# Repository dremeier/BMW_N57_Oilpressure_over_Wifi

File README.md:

# BMW N57 Oilpressure over WiFi

Öldruck- und Öltemperaturanzeige für BMW N57 Motoren auf Basis eines ESP32  
mit eigenem PCB, VDO-Öldrucksensor und Web-UI (Dark-OLED / Kombiinstrument-Stil).

---
## 📸 Projektüberblick

### Komplettsystem – Steuergerät & Sensor

Das System besteht aus einem ESP32-Steuergerät und einer separaten
Sensorplatine, die direkt am VDO-Öldruckgeber montiert ist.  
Die Anzeige erfolgt drahtlos über ein integriertes Web-Interface.

---
### Steuergerät (ESP32-S3 Mini)

## Features

- Messung des **Öldrucks (0–5 bar)** über VDO Druckgeber  
- Messung der **Öltemperatur** (DS18B20)  
- **ESP32 Web-Interface** (kein Internet erforderlich)  
- Automatisches **Tag-/Nacht-Design** (Grün / BMW-Amber)  
- Analoge Rundinstrument-Anzeige (Skala 0–5 bar)  
- Warnlogik:  
  - Öldruck < 0,8 bar → blinkende Warnanzeige  
  - Öltemperatur > Schwellwert → Warnfarbe  
- Integriertes **Debug-Overlay** (ADC, Spannung, Widerstände, Versionen)

---

### VDO Öldruckgeber montiert

OEM-naher VDO-Öldruckgeber mit integrierter Elektronik und KFZ-tauglicher
Montage.

---

## Projektstruktur

```text
BMW_N57_OILPRESSURE_OVER_WIFI/
├─ firmware/          ESP32 Firmware (PlatformIO)
├─ pcb_main/          Hauptplatine (KiCad)
├─ pcb_sensor/        Sensorplatine (KiCad)
├─ docs/              Datenblätter & Dokumentation
└─ README.md
```

---
### 3D-Render – Hauptplatine

3D-Ansicht der Hauptplatine (KiCad).  
Kompaktes, robustes Layout für den Einsatz im Fahrzeug.

## Hardware

- ESP32 (ESP32-S3 mini)
- VDO Öldruckgeber 0–5 bar (M12x1.5)
- DS18B20 Temperatursensor
- Step‑Down‑Regler 
- Versorgung Sensor: **≈ 5,0 V**
- USB‑C zum flaschen

## 🚦 Status-LEDs

| LED | Funktion |
|----|---------|
| **LED orange** | Leuchtet dauerhaft, wenn der WiFi-Access-Point aktiv ist |
| **LED blau** | Leuchtet, sobald ein Client (Smartphone / Browser) verbunden ist |

---

## Messprinzip

Der VDO-Öldruckgeber arbeitet als Widerstand gegen Masse.  
Die Messung erfolgt über einen Spannungsteiler:

```text
+5V → R_PULLUP → Rsensor → GND
```

Die Firmware berechnet:
1. ADC → Spannung (kalibriert)
2. Spannung → Rsensor
3. Rsensor → bar (VDO-Kennlinie via LUT + Interpolation)
4. IIR-Filter zur Glättung

---
### Web-UI (Live-Anzeige)

## Web-UI

- Zugriff über ESP32 Access Point
- Anzeige:
  - Öldruck (bar)
  - Öltemperatur (°C)
  - Analoges Rundinstrument
- Debug-Bereich mit:
  - ADC
  - Vadc
  - Rsensor
  - Bar raw
  - ESP-Temperatur
  - Versorgungsspannung
  - Pullup-Widerstand
  - SW- / HW-Version

---

## Status

- Hardware: **funktionsfähig**
- Firmware: **stabil**
- Kalibrierung: **ADC + Versorgungsspannung kalibriert**
- Projektstatus: **aktiv in Entwicklung**

---

## Hinweis

Dieses Projekt ist ein **DIY-Projekt** und ersetzt keine serienmäßigen
Sicherheitsfunktionen des Fahrzeugs.

Nutzung auf eigene Verantwortung.

---

## Lizenz

Noch nicht festgelegt.

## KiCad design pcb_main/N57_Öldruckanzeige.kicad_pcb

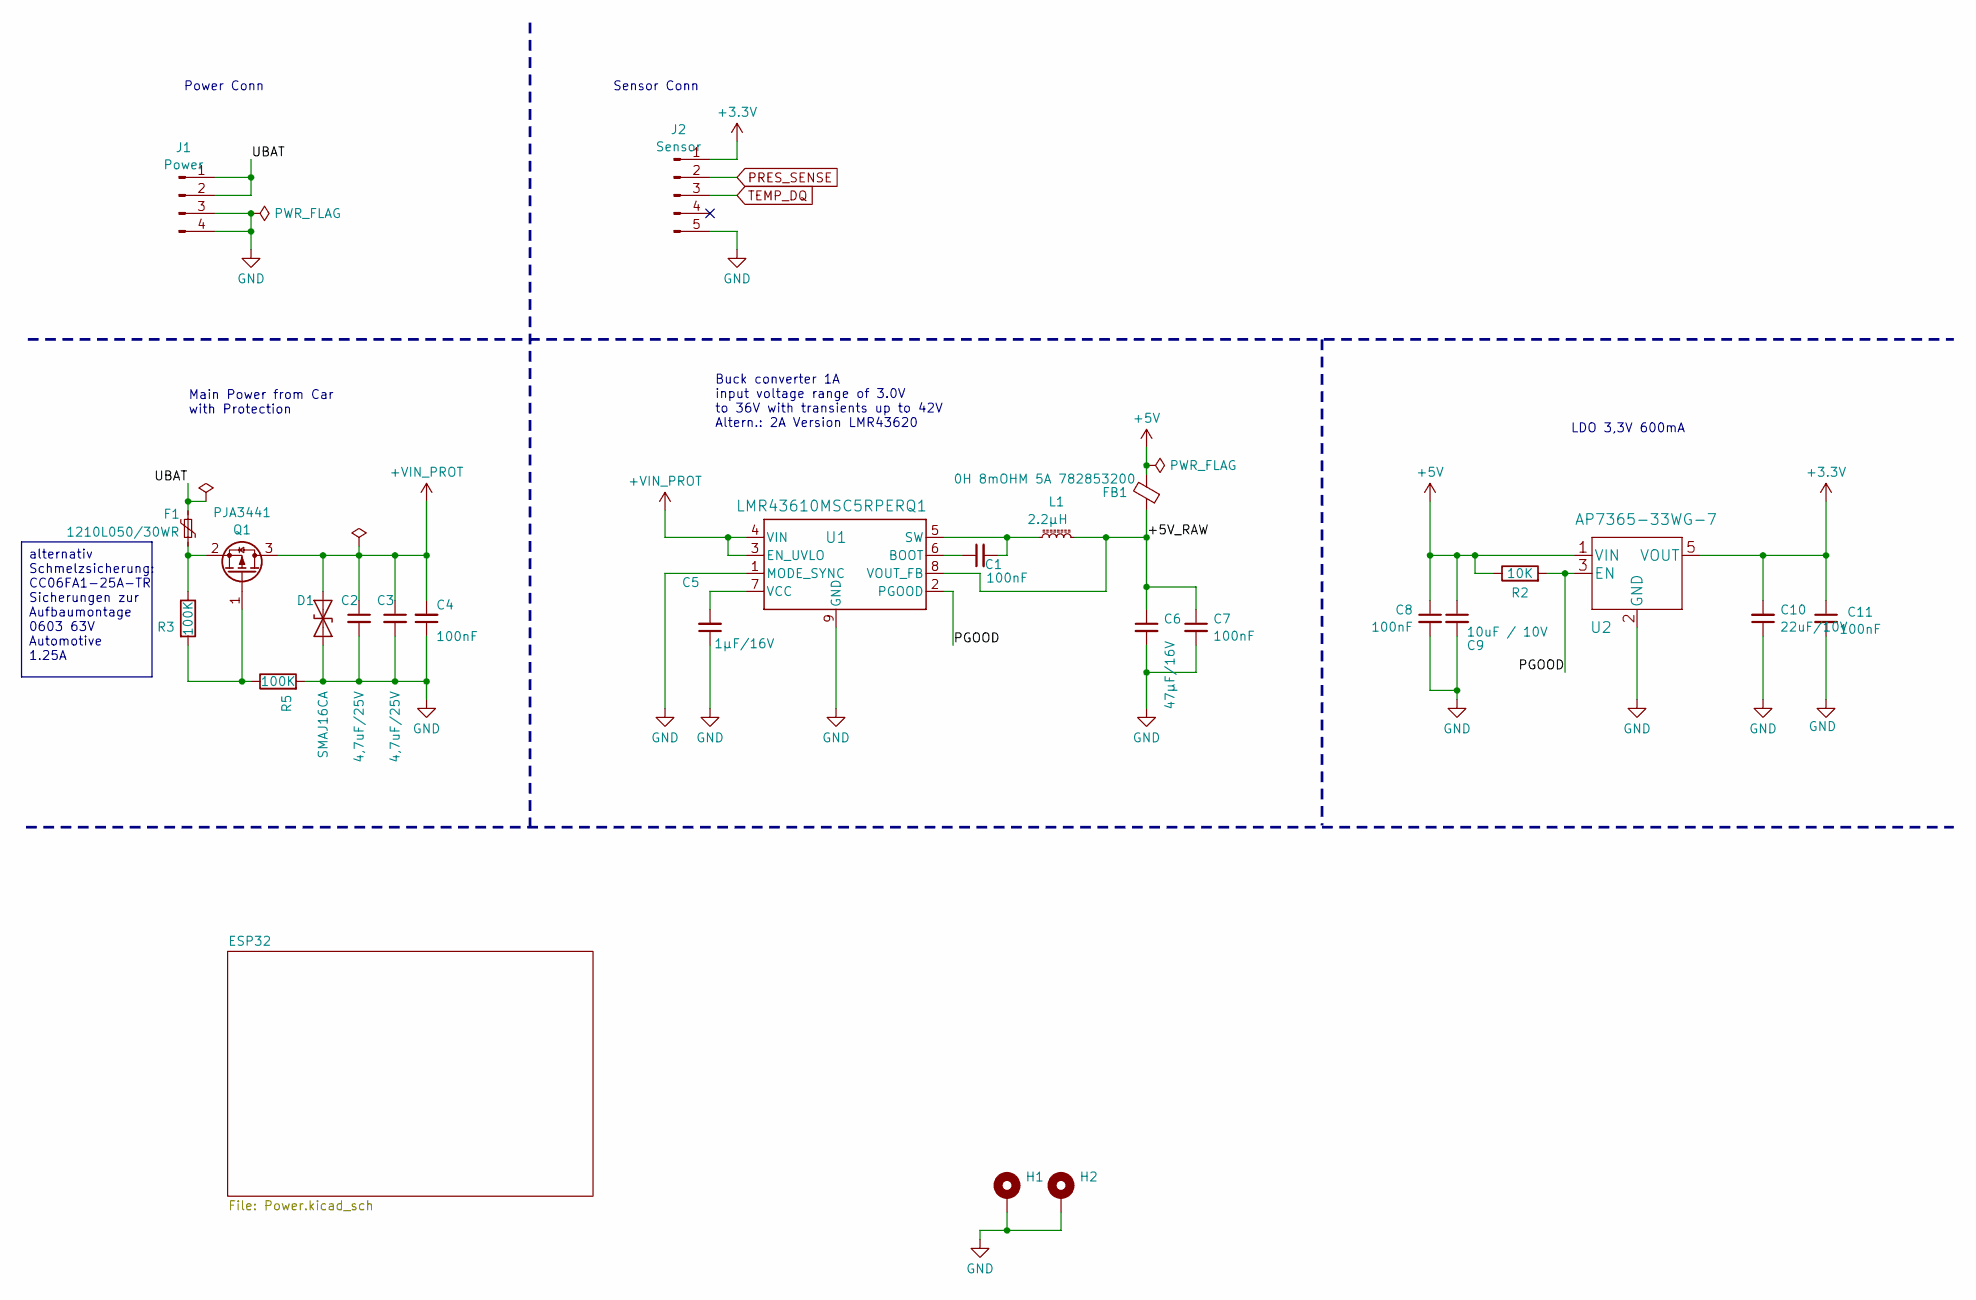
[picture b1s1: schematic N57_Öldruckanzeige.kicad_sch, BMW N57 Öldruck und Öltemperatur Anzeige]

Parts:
C1, C4, C7, C8, C11: 100nF; C_0603_1608Metric; my_parts_ID 5; LCSC C14663
C2, C3: 4,7uF/25V; C_0805_2012Metric; my_parts_ID 37; LCSC C98195
C5: 1μF/16V; C_0603_1608Metric; my_parts_ID 22; LCSC C5199872
C6: 47µF/16V; C_1210_3225Metric; Part Number MBASE32MAB5476KPNDT1; LCSC C77101
C9: 10uF / 10V; C_0805_2012Metric; Part Number GRM21BR71A106KA73K; LCSC C32635
C10: 22uF/10V; C_0603_1608Metric; Part Number GRT188R61A226ME13D; LCSC C86295
D1: SMAJ16CA; D_SMA; Part Number SMAJ40CA-TR; LCSC C148226
F1: 1210L050/30WR; Fuse_1210_3225Metric; Part Number 1210L050/30WR; LCSC C2154034
FB1: 0H 8mOHM 5A 782853200; L_Eaton_MCL2012V1; my_parts_ID 80; LCSC C394484
H1, H2: MountingHole_Pad; MountingHole_3.2mm_M3_ISO7380_Pad
J1: Power; JST_PH_S4B-PH-K_1x04_P2.00mm_Horizontal
J2: Sensor; JST_PH_S5B-PH-K_1x05_P2.00mm_Horizontal
L1: 2.2µH; L_Coilcraft_XxL4040; Part Number XEL4020-222MEC; LCSC C3151182
Q1: PJA3441; SOT-23-3; my_parts_ID 296; LCSC C313504
R2: 10K; R_0603_1608Metric; my_parts_ID 236; LCSC C98220
R3: 100K; R_0603_1608Metric; my_parts_ID 200; LCSC C98220
R5: 100K; R_0603_1608Metric; my_parts_ID 250; LCSC C98220
U1: LMR43610MSC5RPERQ1; LMR43610; Part Number LM61495Q5RPHRQ1; LCSC C5219291
U2: AP7365-33WG-7; SOT-23-5; Part Number AP7365-33WG-7; LCSC C150742

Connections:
+3.3V: C10.2, C11.1, J2.1, U2.5 (VOUT); also elsewhere on the board
+5V: C8.1, C9.1, FB1.2, R2.1, U2.1 (VIN); also elsewhere on the board
+VIN_PROT: C2.1, C3.1, C4.2, D1.2 (A2), Q1.3 (D), U1.3 (EN_UVLO), U1.4 (VIN)
/+5V_RAW: C6.1, C7.1, FB1.1, L1.2, U1.8 (VOUT_FB)
/PGOOD: R2.2, U1.2 (PGOOD), U2.3 (EN)
/UBAT: F1.2, J1.1, J1.2
GND: C2.2, C3.2, C4.1, C5.1, C6.2, C7.2, C8.2, C9.2, C10.1, C11.2, D1.1 (A1), H1.1, H2.1, J1.3, J1.4, J2.5, R5.2, U1.1 (MODE_SYNC), U1.9 (GND), U2.2 (GND); also elsewhere on the board
unnamed: Q1.1 (G), R3.2, R5.1
unnamed: F1.1, Q1.2 (S), R3.1
unnamed: C1.1, U1.6 (BOOT)
unnamed: C1.2, L1.1, U1.5 (SW)
unnamed: C5.2, U1.7 (VCC)
PRES_SENSE: J2.2; also elsewhere on the board
TEMP_DQ: J2.3; also elsewhere on the board

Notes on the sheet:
Sensor Conn
Main Power from Car with Protection
Power Conn
LDO 3,3V 600mA
Buck converter 1A input voltage range of 3.0V to 36V with transients up to 42V Altern.: 2A Version LMR43620
alternativ Schmelzsicherung: CC06FA1-25A-TR Sicherungen zur Aufbaumontage 0603 63V Automotive 1.25A

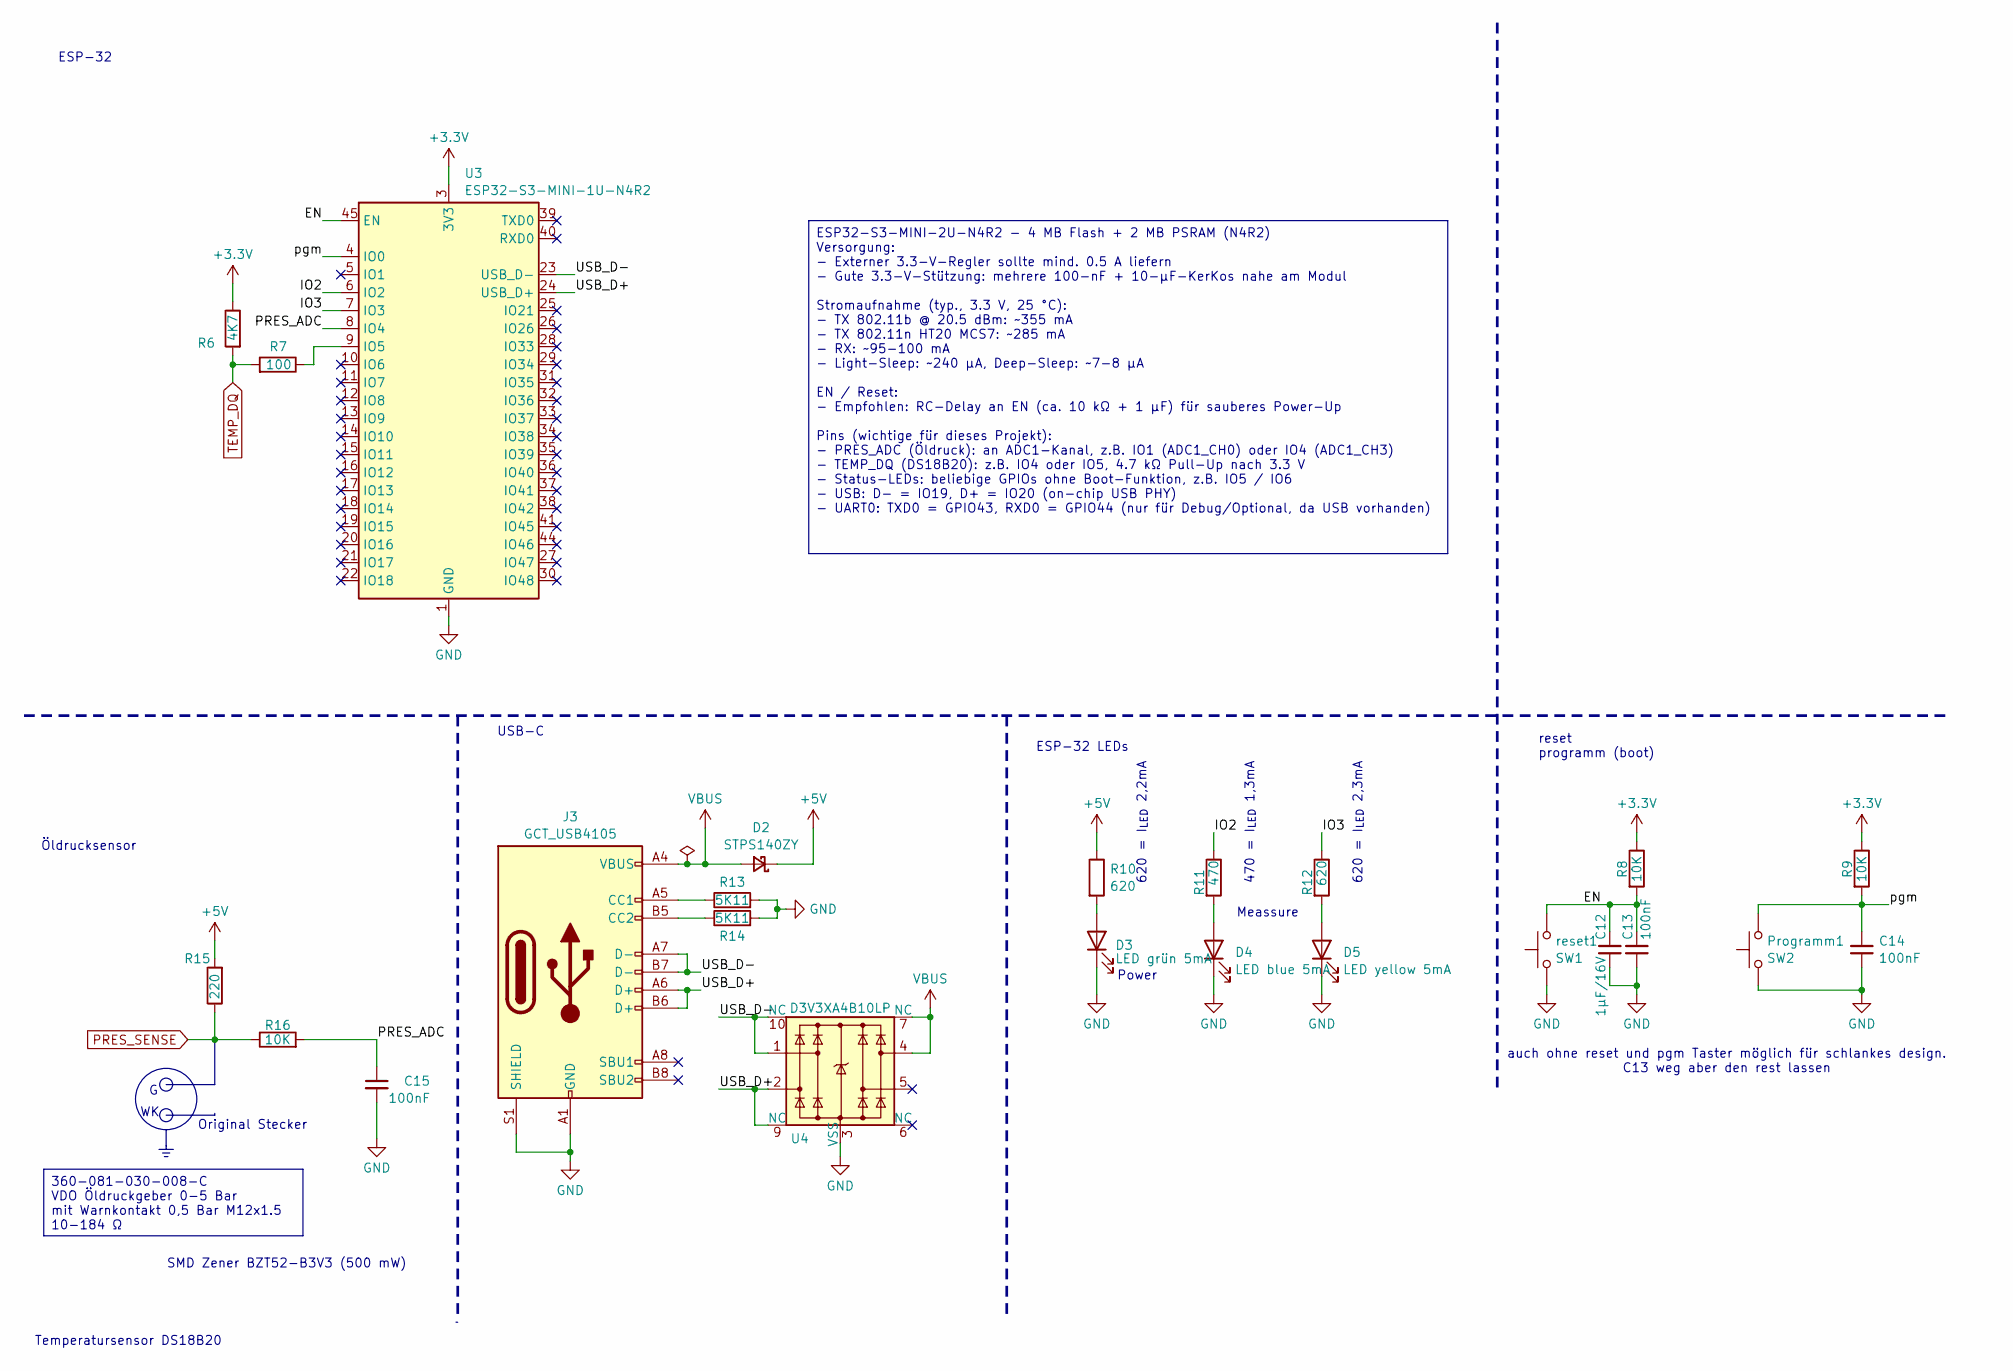
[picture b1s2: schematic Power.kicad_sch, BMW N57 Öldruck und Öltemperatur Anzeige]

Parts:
C12: 1μF/16V; C_0603_1608Metric; my_parts_ID 22; LCSC C5199872
C13, C14, C15: 100nF; C_0603_1608Metric; my_parts_ID 5; LCSC C14663
D2: STPS140ZY; D_SOD-123; my_parts_ID 71; LCSC C155662
D3: LED grün 5mA; LED_0603_1608Metric; my_parts_ID 184; LCSC C2962098
D4: LED blue 5mA; LED_0603_1608Metric; my_parts_ID 182; LCSC C125103
D5: LED yellow 5mA; LED_0603_1608Metric; my_parts_ID 183; LCSC C160477
J3: GCT_USB4105; USB_C_Receptacle_GCT_USB4105-xx-A_16P_TopMnt_Horizontal; Part Number USB4105-GF-A-120; LCSC C5184243
Programm1: SW2; SW_Push_1P1T_NO_Vertical_Wuerth_434133025816; Part Number RKB2SJK250SMTR; LCSC C2927789
R6: 4K7; R_0603_1608Metric; my_parts_ID 246; LCSC C99782
R7: 100; R_0603_1608Metric; my_parts_ID 200; LCSC C105588
R8, R9: 10K; R_0603_1608Metric; my_parts_ID 236; LCSC C98220
R10, R12: 620; R_0603_1608Metric; my_parts_ID 220; LCSC C137695
R11: 470; R_0603_1608Metric; my_parts_ID 216; LCSC C114669
R13, R14: 5K11; R_0603_1608Metric; my_parts_ID 233; LCSC C112314
R15: 220; R_0603_1608Metric; my_parts_ID 207; LCSC C107696
R16: 10K; R_0603_1608Metric; my_parts_ID 207; LCSC C107696
U3: ESP32-S3-MINI-1U-N4R2; ESP32-S2-MINI-1U; my_parts_ID 298; LCSC C22356044
U4: D3V3XA4B10LP; Diodes_UDFN-10_1.0x2.5mm_P0.5mm; Part Number D3V3XA4B10LP-7; LCSC C1980462
reset1: SW1; SW_Push_1P1T_NO_Vertical_Wuerth_434133025816; Part Number RKB2SJK250SMTR; LCSC C2927789

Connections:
+3.3V: R6.1, R8.1, R9.1, U3.3 (3V3); also elsewhere on the board
+5V: D2.1 (K), R10.1, R15.2; also elsewhere on the board
/ESP32/EN: C12.2, C13.2, R8.2, U3.45 (EN), reset1.2
/ESP32/IO2: R11.1, U3.6 (IO2)
/ESP32/IO3: R12.1, U3.7 (IO3)
/ESP32/PRES_ADC: C15.1, R16.2, U3.8 (IO4)
/ESP32/USB_D+: J3.A6 (D+), J3.B6 (D+), U3.24 (USB_D+), U4.2, U4.9 (NC)
/ESP32/USB_D-: J3.A7 (D-), J3.B7 (D-), U3.23 (USB_D-), U4.1, U4.10 (NC)
/ESP32/pgm: C14.2, Programm1.2, R9.2, U3.4 (IO0)
GND: C12.1, C13.1, C14.1, C15.2, D3.1 (K), D4.1 (K), D5.1 (K), J3.A1 (GND), J3.A12 (GND), J3.B1 (GND), J3.B12 (GND), J3.S1 (SHIELD), Programm1.1, R13.2, R14.2, U3.1 (GND), U3.2 (GND), U3.42 (GND), U3.43 (GND), U3.46 (GND), U3.47 (GND), U3.48 (GND), U3.49 (GND), U3.50 (GND), U3.51 (GND), U3.52 (GND), U3.53 (GND), U3.54 (GND), U3.55 (GND), U3.56 (GND), U3.57 (GND), U3.58 (GND), U3.59 (GND), U3.60 (GND), U3.61 (GND), U3.62 (GND), U3.63 (GND), U3.64 (GND), U3.65 (GND), U4.3 (VSS), reset1.1; also elsewhere on the board
unnamed: D3.2 (A), R10.2
unnamed: D4.2 (A), R11.2
unnamed: D5.2 (A), R12.2
unnamed: J3.A5 (CC1), R13.1
unnamed: J3.B5 (CC2), R14.1
unnamed: R7.1, U3.9 (IO5)
PRES_SENSE: R15.1, R16.1; also elsewhere on the board
TEMP_DQ: R6.2, R7.2; also elsewhere on the board
VBUS: D2.2 (A), J3.A4 (VBUS), J3.A9 (VBUS), J3.B4 (VBUS), J3.B9 (VBUS), U4.4, U4.7 (NC)

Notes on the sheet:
auch ohne reset und pgm Taster möglich für schlankes design. C13 weg aber den rest lassen
Meassure
Temperatursensor DS18B20
reset programm (boot)
ESP-32
620 = I_{LED} 2,2mA
Power
ESP-32 LEDs
620 = I_{LED} 2,3mA
SMD Zener BZT52-B3V3 (500 mW)
Original Stecker
Öldrucksensor
470 = I_{LED} 1,3mA
USB-C
ESP32-S3-MINI-2U-N4R2 - 4 MB Flash + 2 MB PSRAM (N4R2) Versorgung: - Externer 3.3-V-Regler sollte mind. 0.5 A liefern - Gute 3.3-V-Stützung: mehrere 100-nF + 10-µF-KerKos nahe am Modul Stromaufnahme (typ., 3.3 V, 25 °C): - TX 802.11b @ 20.5 dBm: ~355 mA - TX 802.11n HT20 MCS7: ~285 mA - RX: ~95-100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
360-081-030-008-C VDO Öldruckgeber 0-5 Bar mit Warnkontakt 0,5 Bar M12x1.5 10-184 Ω

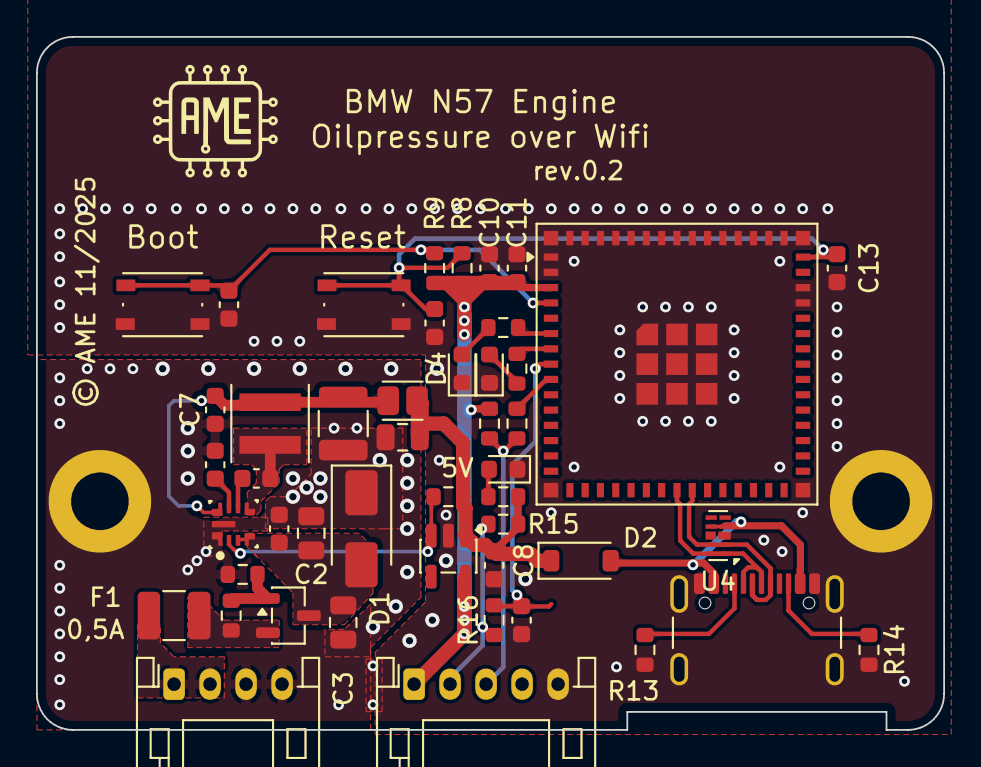
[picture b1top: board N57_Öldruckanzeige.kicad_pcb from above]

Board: 2 copper layers, 50.4 x 38.5 mm, 49 parts (0 on the bottom side), 28 nets.

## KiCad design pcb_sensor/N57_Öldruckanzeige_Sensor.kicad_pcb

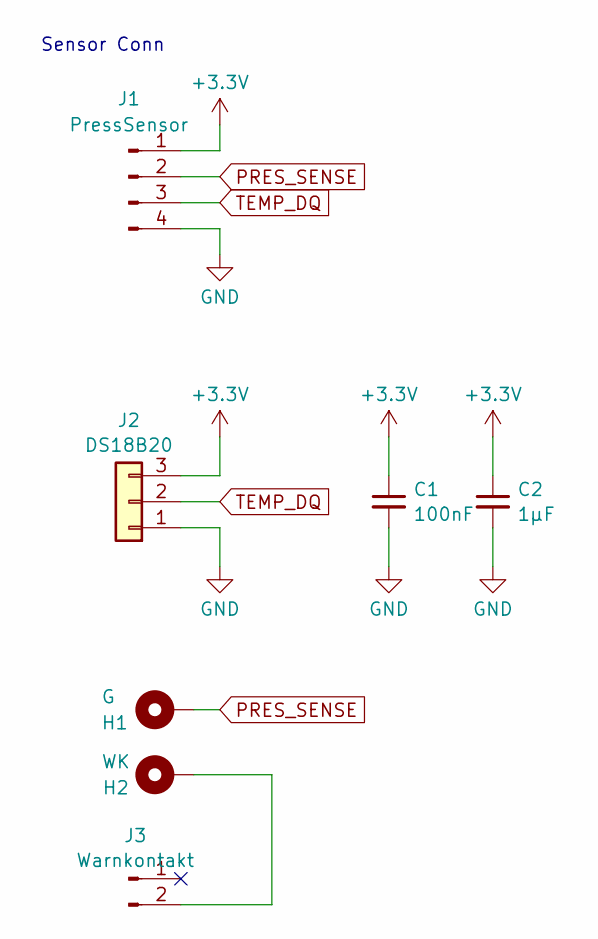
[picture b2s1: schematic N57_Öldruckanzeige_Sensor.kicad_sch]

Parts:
C1: 100nF; C_0603_1608Metric_Pad1.08x0.95mm_HandSolder
C2: 1μF; C_0603_1608Metric_Pad1.08x0.95mm_HandSolder
H1: G; MountingHole_4.3x6.2mm_M4_Pad
H2: WK; MountingHole_4.3x6.2mm_M4_Pad
J1: PressSensor; JST_PH_S4B-PH-K_1x04_P2.00mm_Horizontal
J2: DS18B20; PinHeader_1x03_P2.00mm_Vertical
J3: Warnkontakt; KFZ-2-POL-P5_DJ7021B-3.5-1121

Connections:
+3.3V: C1.1, C2.1, J1.1, J2.3
GND: C1.2, C2.2, J1.4, J2.1
unnamed: H2.1, J3.2
PRES_SENSE: H1.1, J1.2
TEMP_DQ: J1.3, J2.2

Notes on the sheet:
Sensor Conn

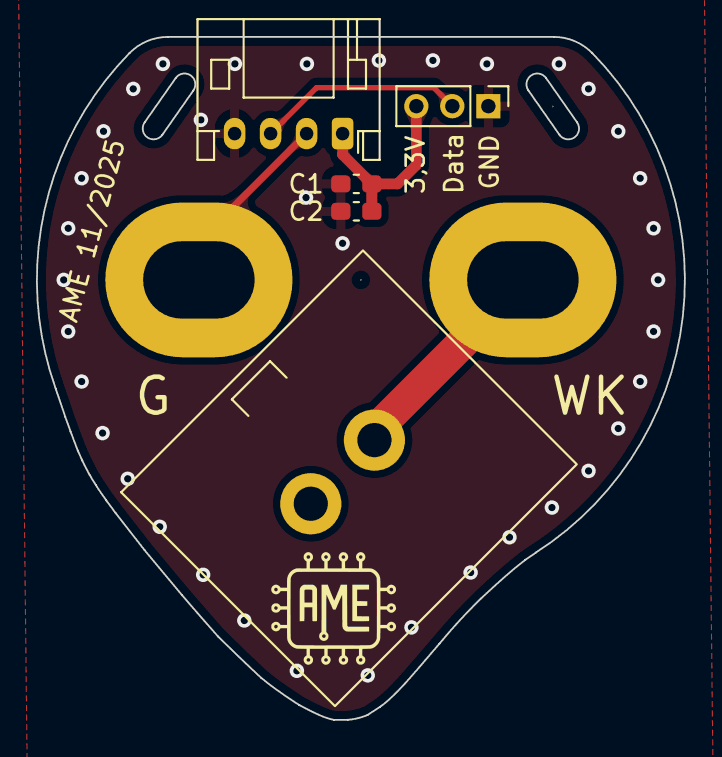
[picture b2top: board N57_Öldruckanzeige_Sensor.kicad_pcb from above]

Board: 2 copper layers, 36.0 x 37.9 mm, 7 parts (0 on the bottom side), 5 nets.

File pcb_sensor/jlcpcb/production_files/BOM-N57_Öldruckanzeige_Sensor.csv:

Comment,Designator,Footprint,LCSC,Quantity
Conn_01x02_Pin,J3,KFZ-2-POL-P5_DJ7021B-3.5-1121,,1
1μF,C2,C_0603_1608Metric_Pad1.08x0.95mm_HandSolder,,1
DS18B20,J2,PinHeader_1x03_P2.00mm_Vertical,,1
100nF,C1,C_0603_1608Metric_Pad1.08x0.95mm_HandSolder,,1
PressSensor,J1,JST_PH_S4B-PH-K_1x04_P2.00mm_Horizontal,,1

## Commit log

2025-12-15 Initial commit: ESP32 firmware and PCB design
2025-12-15 add readme
2025-12-15 add pics and update README
2025-12-15 V1.1 add ticks to the arc in Web-UI
2025-12-15 V1.1 add coments

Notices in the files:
pcb_main/N57_Öldruckanzeige.kicad_pcb:
© AME 11/2025
